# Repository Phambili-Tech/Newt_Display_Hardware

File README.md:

# Newt

The Newt is an always-on, low-powered, mountable display that can be connected to the internet to retrieve weather, calendars, sports scores, todo lists, quotes... really anything that is available on the web! The Newt is powered by an ESP32-S2 microcontroller that can be programmed with Arduino, CircuitPython, and ESP-IDF.

We consider the Newt to be the next evolution of the popular eInk displays that makers love to tinker with. We use a SHARP Memory In Pixel LCD in order to avoid the slow refresh times of eInk. We've added a Real Time Clock to support alarms and timers. Finally, we designed the Newt with battery operation in mind;  every component on the board was chosen for it's ability to operate at low power.

**Lists of product features and/or specifications:**

The Newt is designed to operate for 1-2 months between charges (using a 500 mAH Lipo). The amount of time varies between usage; heavier WiFi usage will more quickly reduce battery charge.

Microcontroller:
- Espressif ESP32-S2-WROVER Module with 4 MB flash and 2 MB PSRAM
- WiFi capable
- Supports Arduino, CircuitPython, and ESP-IDF
- Deep Sleep current as low as 25 uA

Display:
- 2.7 inch 240x400 SHARP Memory In Pixel LCD
- Capable of delivering high-contrast, high-resolution content with ultra-low power consumption
- Reflective mode leverages ambient light to eliminate the need for a backlight

Time Keeping, Timers, and Alarms:
- Micro Crystal RV-3028-C7 Real Time Clock
- Optimized for extreme low power consumption (45 nanoAmps)
- Able to simultaneously manage periodic timer, countdown timer, and alarm
- Hardware interrupt for timers and alarms
- 43 bytes non-volatile user memory, 2 bytes user RAM
- Separate UNIX time counter

Buzzer:
- Speaker/Buzzer with mini class D amplifier on DAC output A0 can play tones or lo-fi audio clips

User Interaction:
- 10 capacitive touch pads
- On/off switch
- Reset and Boot tactile buttons for reprogramming

Power:
- USB Type-C connector for programming, power, and charging
- Low quiescence Voltage Regulator (TOREX XC6220) that can output 1A of current and operate as low as 8 uA.
- JST connector for Lithium-Ion battery
- Battery charging circuity (MCP73831)
- Low Battery indicator (1 uA quiescence current)

PCB and Display dimensions:
- 91 mm x 61mm x 9mm

Software:
- Newt hardware compatible with open-source Arduino libraries for ESP32-S2, Adafruit GFX (fonts), Adafruit Sharp Memory Display (display writing), and RTC RV-3028-C7 (rtc)
- Newt Arduino library and sample programs in progress; will be available on Githib before launch
- Newt CircuitPython libraries and registration on the roadmap (key dependency is the development of CircuitPython library for the RV-3028 real time clock)

Optional Mounting and Desktop Hardware:
- Acrylic Mounting Bracket with magnetic fixtures and expander for "flat" lithium-Ion batteries (up to 2500mAh)
- Putty for non-magnetic adhesion
- Stand for desk or nightstand (made from engineered wood)

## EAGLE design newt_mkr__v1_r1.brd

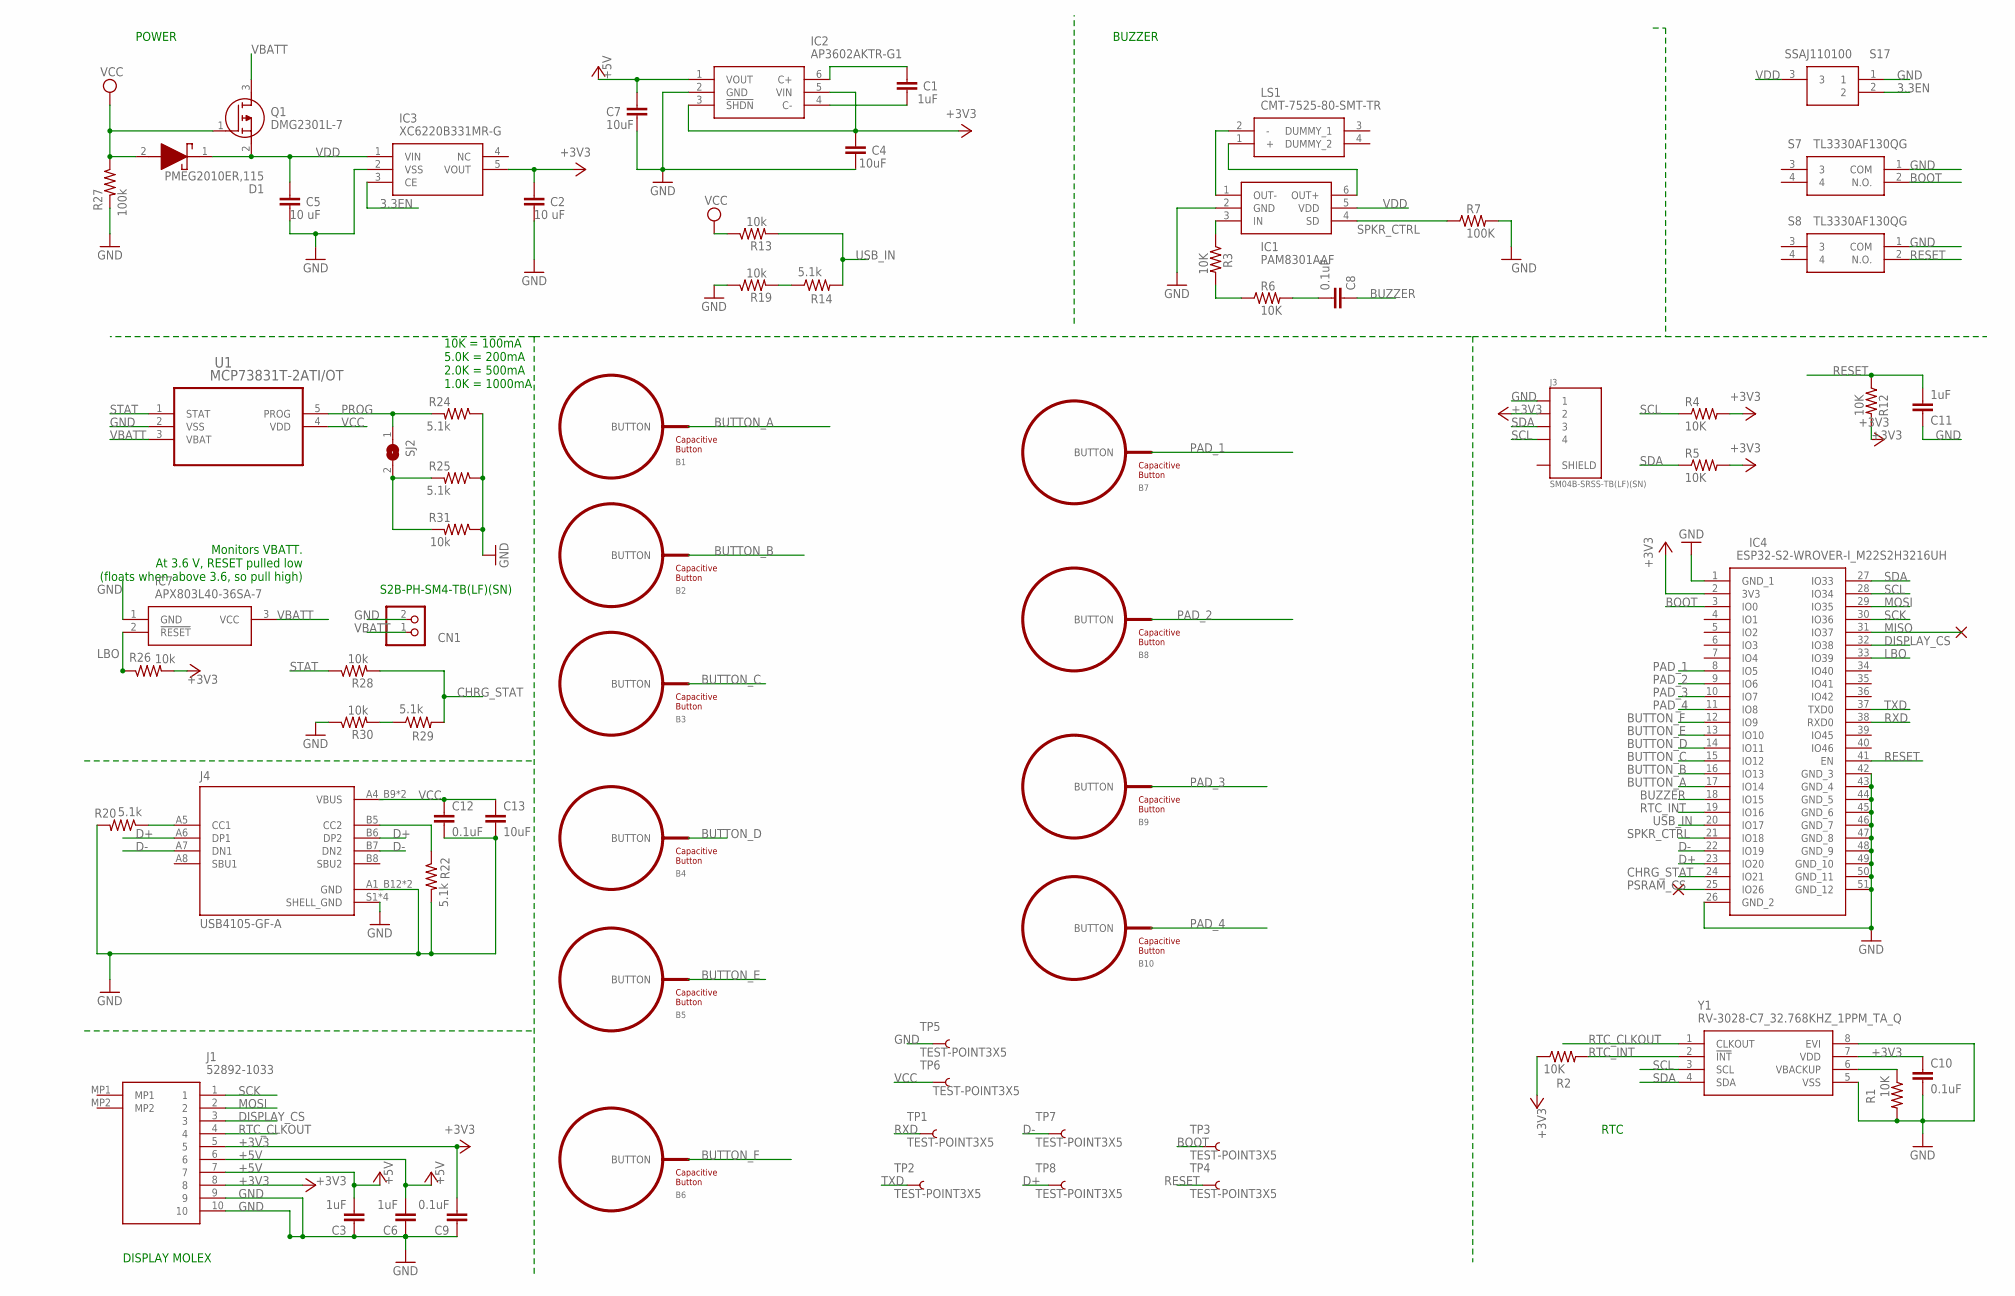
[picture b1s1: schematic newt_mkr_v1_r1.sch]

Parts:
B1, B2, B3, B4, B5, B6: BUTTON_PASSIVE6MM; BUTTON_PASSIVE_6MM
B7, B8, B9, B10: BUTTON_PASSIVE10MM; BUTTON_PASSIVE_10MM
C1, C3, C6, C11: 1uF; C0603
C2, C5: 10 uF; C0603
C4, C7, C13: 10uF; C0603
C8, C9, C10, C12: 0.1uF; C0603
CN1: JST_2PIN-SMT-RA; JST-PH-2-SMT-RA
D1: PMEG2010ER,115; SODFL3517X110N
IC1: PAM8301AAF; SOT95P280X145-6N
IC2: AP3602AKTR-G1; SOT95P280X145-6N
IC3: XC6220B331MR-G; SOT95P280X130-5N
IC4: ESP32-S2-WROVER-I_M22S2H3216UH; ESP32S2WROVERIM22S2H3216UH3Q0
IC7: APX803L40-36SA-7; SOT96P240X110-3N
J1: 52892-1033; 528921033
J3: SM04B-SRSS-TB(LF)(SN); JST_SM04B-SRSS-TB(LF)(SN)
J4: USB4105-GF-A; GCT_USB4105-GF-A
LS1: CMT-7525-80-SMT-TR; CMT752580SMTTR
Q1: DMG2301L-7; SOT96P240X110-3N
R1, R2, R3, R4, R5, R6, R12: 10K; R0603
R7: 100K; R0603
R13, R19, R26, R28, R30, R31: 10k; R0603
R14, R20, R22, R24, R25, R29: 5.1k; R0603
R27: 100k; R0603
S7, S8: TL3330AF130QG
S17: SSAJ110100; SSAJ110100_1
SJ2: MICROBUILDER_SOLDERJUMPERCLOSED; MICROBUILDER_SOLDERJUMPER_CLOSEDWIRE
TP1, TP2, TP3, TP4, TP5, TP6, TP7, TP8: TEST-POINT3X5; PAD.03X.05
U1: MCP73831T-2ATI/OT; SOT95P300X145-5N
Y1: RV-3028-C7_32.768KHZ_1PPM_TA_Q; RV-8803-C7

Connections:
3.3EN: IC3.3 (CE), S17.2
+3V3: C2.2, C4.2, C9.2, C10.1, IC2.3 (!SHDN), IC2.5 (VIN), IC3.5 (VOUT), IC4.2 (3V3), J1.5, J1.8, J3.2, R2.1, R4.2, R5.2, R12.2, R26.2, Y1.7 (VDD)
+5V: C3.2, C6.2, C7.2, IC2.1 (VOUT), J1.6, J1.7
BOOT: IC4.3 (IO0), S7.2 (N.O.), TP3.P$1
BUTTON_A: B1.BUTTON, IC4.17 (IO14)
BUTTON_B: B2.BUTTON, IC4.16 (IO13)
BUTTON_C: B3.BUTTON, IC4.15 (IO12)
BUTTON_D: B4.BUTTON, IC4.14 (IO11)
BUTTON_E: B5.BUTTON, IC4.13 (IO10)
BUTTON_F: B6.BUTTON, IC4.12 (IO9)
BUZZER: C8.1, IC4.18 (IO15)
CC2: J4.B5 (CC2), R22.1
CHRG_STAT: IC4.24 (IO21), R28.2, R29.2
D+: IC4.23 (IO20), J4.A6 (DP1), J4.B6 (DP2), TP8.P$1
D-: IC4.22 (IO19), J4.A7 (DN1), J4.B7 (DN2), TP7.P$1
DISPLAY_CS: IC4.32 (IO38), J1.3
GND: C2.1, C3.1, C4.1, C5.1, C6.1, C7.1, C9.1, C10.2, C11.1, C12.2, C13.2, CN1.2 (1), IC1.2 (GND), IC2.2 (GND), IC3.2 (VSS), IC4.1 (GND_1), IC4.26 (GND_2), IC4.42 (GND_3), IC4.43 (GND_4), IC4.44 (GND_5), IC4.45 (GND_6), IC4.46 (GND_7), IC4.47 (GND_8), IC4.48 (GND_9), IC4.49 (GND_10), IC4.50 (GND_11), IC4.51 (GND_12), IC7.1 (GND), J1.9, J1.10, J3.1, J4.A1_B12 (GND), J4.B1_A12 (GND), J4.S1 (SHELL_GND), J4.S2 (SHELL_GND), J4.S3 (SHELL_GND), J4.S4 (SHELL_GND), R1.2, R7.2, R19.1, R20.2, R22.2, R24.1, R25.1, R27.2, R30.1, R31.1, S7.1 (COM), S8.1 (COM), S17.1, TP5.P$1, U1.2 (VSS), Y1.5 (VSS), Y1.8 (EVI)
LBO: IC4.33 (IO39), IC7.2 (!RESET), R26.1
MISO: IC4.31 (IO37)
MOSI: IC4.29 (IO35), J1.2
unnamed: IC1.6 (OUT+), LS1.1 (+)
unnamed: IC1.1 (OUT-), LS1.2 (-)
unnamed: R1.1, Y1.6 (VBACKUP)
unnamed: R14.1, R19.2
unnamed: C1.2, IC2.6 (C+)
unnamed: C1.1, IC2.4 (C-)
unnamed: IC1.3 (IN), R3.1
unnamed: R29.1, R30.2
unnamed: R25.2, R31.2, SJ2.2
unnamed: R3.2, R6.1
unnamed: C8.2, R6.2
unnamed: J4.A5 (CC1), R20.1
PAD_1: B7.BUTTON, IC4.8 (IO5)
PAD_2: B8.BUTTON, IC4.9 (IO6)
PAD_3: B9.BUTTON, IC4.10 (IO7)
PAD_4: B10.BUTTON, IC4.11 (IO8)
PROG: R24.2, SJ2.1, U1.5 (PROG)
PSRAM_CS: IC4.25 (IO26)
RESET: C11.2, IC4.41 (EN), R12.1, S8.2 (N.O.), TP4.P$1
RTC_CLKOUT: J1.4, Y1.1 (CLKOUT)
RTC_INT: IC4.19 (IO16), R2.2, Y1.2 (!INT)
RXD: IC4.38 (RXD0), TP1.P$1
SCK: IC4.30 (IO36), J1.1
SCL: IC4.28 (IO34), J3.4, R4.1, Y1.3 (SCL)
SDA: IC4.27 (IO33), J3.3, R5.1, Y1.4 (SDA)
SPKR_CTRL: IC1.4 (SD), IC4.21 (IO18), R7.1
STAT: R28.1, U1.1 (STAT)
TXD: IC4.37 (TXD0), TP2.P$1
USB_IN: IC4.20 (IO17), R13.2, R14.2
VBATT: CN1.1 (2), IC7.3 (VCC), Q1.3 (D), U1.3 (VBAT)
VCC: C12.1, C13.1, D1.2 (A), J4.A4_B9 (VBUS), J4.B4_A9 (VBUS), Q1.1 (G), R13.1, R27.1, TP6.P$1, U1.4 (VDD)
VDD: C5.2, D1.1 (K), IC1.5 (VDD), IC3.1 (VIN), Q1.2 (S), S17.3

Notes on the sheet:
POWER
DISPLAY MOLEX
RTC
Monitors VBATT. At 3.6 V, RESET pulled low (floats when above 3.6, so pull high)
S2B-PH-SM4-TB(LF)(SN)‎
10K = 100mA 5.0K = 200mA 2.0K = 500mA 1.0K = 1000mA
BUZZER

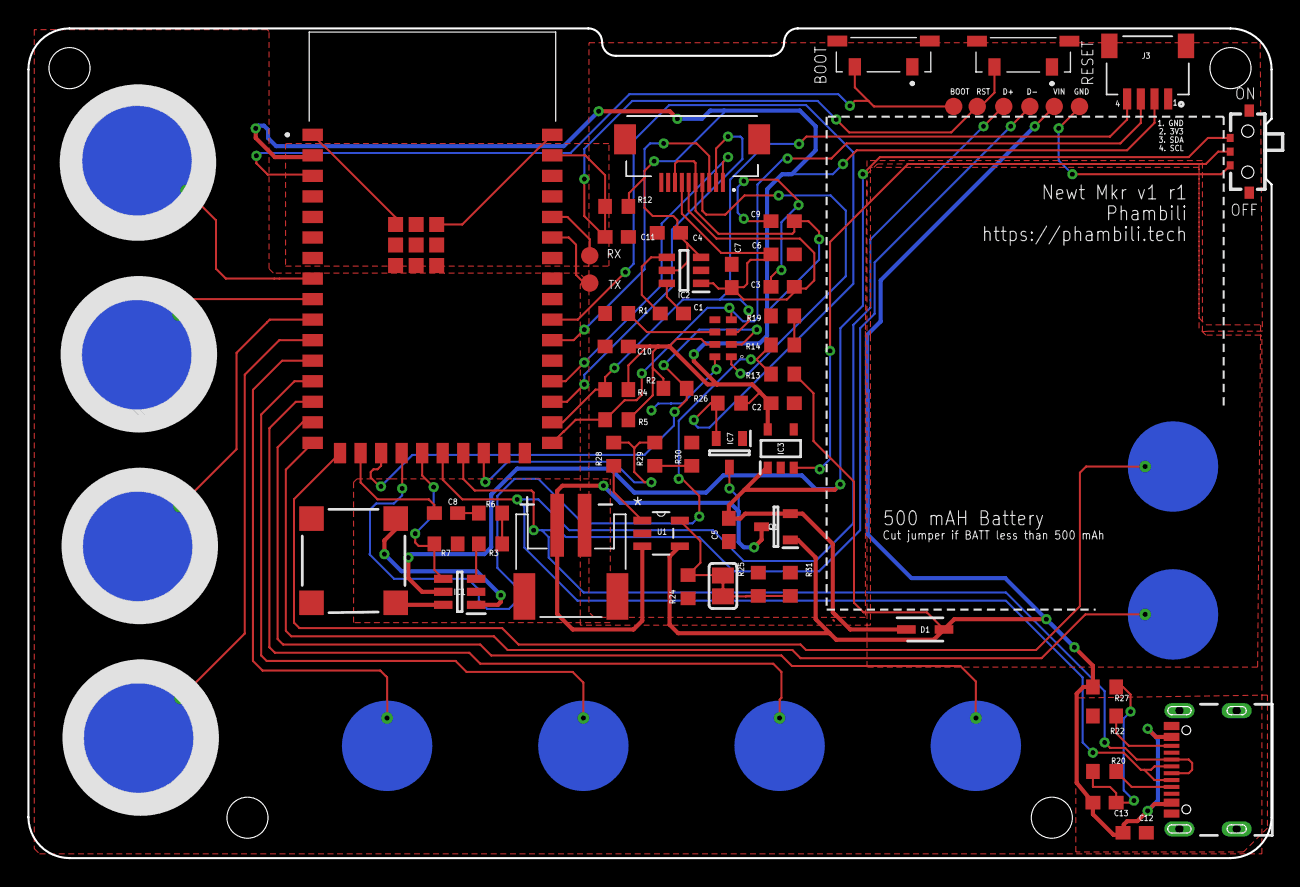
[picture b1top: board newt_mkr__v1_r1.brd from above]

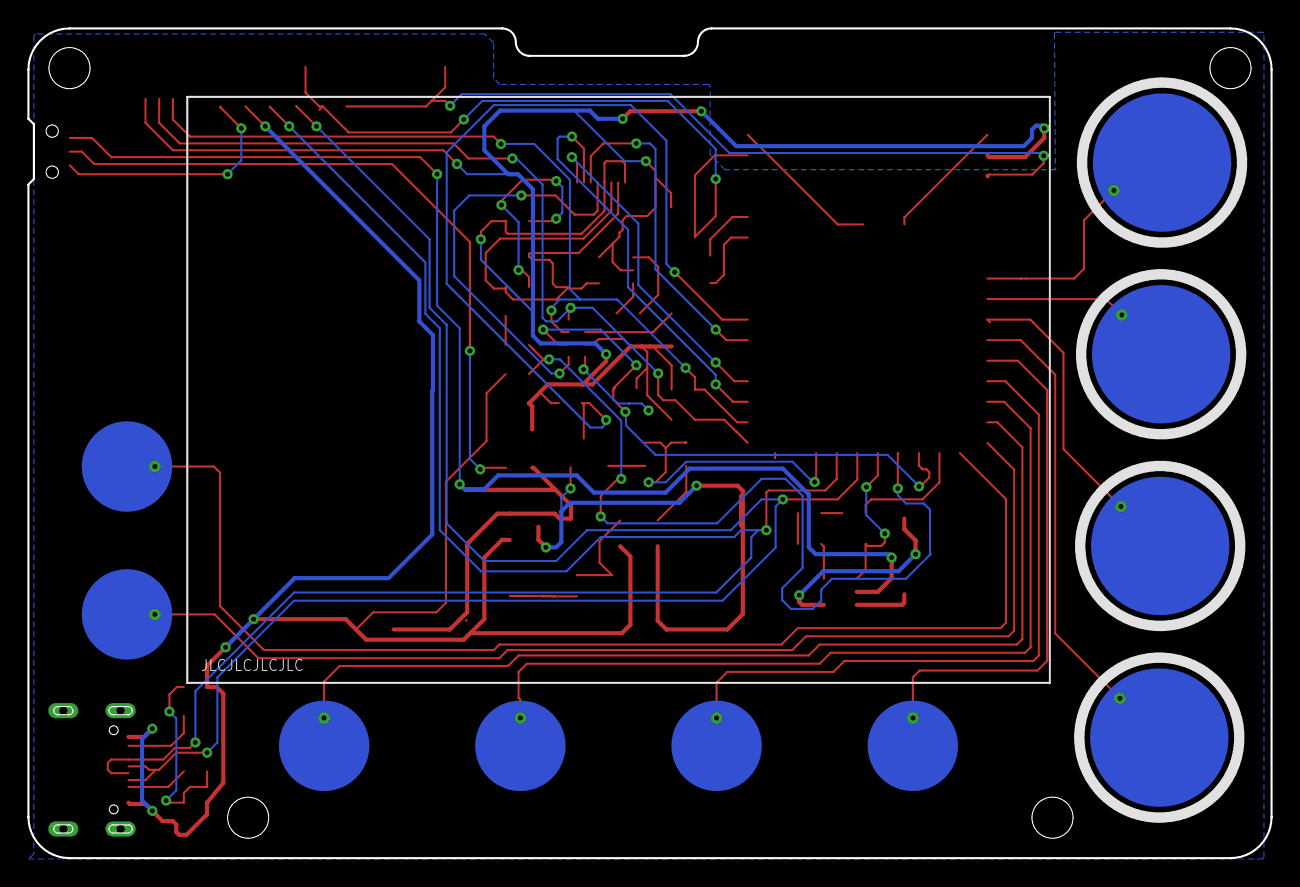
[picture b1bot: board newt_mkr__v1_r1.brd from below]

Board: 2 copper layers, 90.8 x 60.6 mm, 70 parts (10 on the bottom side), 50 nets.

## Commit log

2021-09-25 tweak to readme
2021-09-26 Added image assets
2021-09-26 resized images
2021-09-26 added eagle files
2021-09-26 added schematic in png
2021-09-26 Rename eagle board
2021-09-26 added Fusion 360 archive
2022-03-29 Tester binary file for Newt
    Tester version 0.0.8 for Newt (for factory testing to confirm screen, RTC, and buzzer)
2022-04-05 Tester and Version 0.0.9 for software
2022-04-07 v11 software
2022-08-11 Step, Obj, and STL files for Newt Board

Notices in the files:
parts and their libraries:
PatternAgents-TouchWidgets: License : http://creativecommons.org/licenses/by-sa/4.0/ (Creative Commons 4.0)
PatternAgents-TouchWidgets: License : http://creativecommons.org/licenses/by-sa/3.1/ (Creative Commons 3.1)
